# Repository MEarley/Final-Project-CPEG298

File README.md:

# Internet of Things Device for a Microbial Fuel Cell: IoT MFC
The purpose of this device is to measure the voltage and the surrounding environment of the said cell for research purposes.

## Schematic of SMART MFC (KiCAD)

## SMART MFC CAM
### Front 									

### Back

## SMART MFC BOM

## Arduino code
The entire Arduino sketch is divided into 3 main functions: setup(), loop(), and espData(). 

##### Note: There is also a very minor calculateVoltage() function. However, this is rather self-explanatory. 

The setup() function begins by setting up the serial monitor and the ESP8266 to a baud rate of 9600. Using the ESP8266, it connects to the internet to access Adafruit IO using both usernames and passwords given by the user. After the ESP8266 has successfully connected to Adafruit, analog pins for the light sensor, soil moisture sensor, and voltage reader are set. In addition, the DHT20 is set up using the freely accessible library by Rob Tillaart.

Within the loop() function, the entire block of code repeats every ~5 seconds. This delay is due to the fact that Adafruit only allows a maximum of 30 uploads/minute for free. Using the analogRead() function from the Arduino library, the Arduino Uno collects data in relation to the light, soil moisture, and voltage levels. In addition, the DHT20 library is used to get the humidity and temperature values from the DHT20 sensor. After each reading, the data is transmitted through the ESP8266 to Adafruit where it can be graphically displayed. This loop() function also sets threshold values for the soil moisture level and the temperature values.

Within the espData() function, the given command and data are sent to the ESP8266 using Serial UART. After the data has been sent, the function waits for a response from the ESP8266. This leads to the function printing out the response within the Serial Monitor where it can be viewed for debugging purposes.

## Libraries and Additional Sources
 • Arduino.h
 
 • Wire.h

 • SoftwareSerial.h | Allows usage of two GPIO pins for a second UART

 • DHT20.h | Allows for easier usage of the DHT20
   ESP8266 Example program provided by Theo Fleck and Rick Martin
   DHT20 Demo code provided by library author Rob Tillaart

## Adafruit Dashboard

### Line Graphs

 • Light Level | Displays the level of light over a given time interval time

 • Soil Moisture Level | Displays the level of moisture in the soil over a given time interval time

 • Voltage | Displays the voltage in millivolts of the MFC in a given time interval time   
### Circle Graphs

 • Soil Moisture Level | Displays the current level of moisture within the soil with thresholds between 250 - 700

 • Temperature | Displays the current temperature with a threshold between 20 - 55℃
### Indicators

 • Soil Moisture Level | Indicates when the current soil moisture level is over 250

•  Temperature Level | Indicates when the current temperature is below 25℃

•  Humidity Bar Graph | Displays current relative humidity

•  Feed | Displays data messages between Adafruit and the ESP8266

## Future Changes
In terms of redesign, the voltmeter on the reader still requires tweaking and is the only leading cause of concern. Its purpose in this project is to measure the produced voltage from a Microbial Fuel Cell, which in itself is like a battery having both a positive and negative node. The rise of concern comes from trying to read the amount of voltage produced by the said battery. The Microbial Fuel Cells, or MFC, that are being used in this report can range from 1 mV to 100 mV or more. 

At first, I attempted to read the voltage directly using analogRead(). However, the voltage could not be read due to the voltage being too small. After further research, I came to the conclusion of two possible solutions. 

Solution #1 is an op-amp with a high gain. However, with a capped supply voltage of 5V and a high range of 1-100+ mV, deciding an appropriate gain may be tricky. This would also require additional wiring and spacing for the PCB layout. 

While Solution #1 has a more hardware approach, Solution #2 approaches the problem through the software and proved to be more successful to an extent. Solution #2 is what is seen in the current design: the calculateVoltage() function. This function changes the reference voltage from the default 5V to 1,1V. This allows me to measure the number of millivolts directly from the MFC. While experimenting with a standalone program and an empty Arduino board, this solution works fine. However, in practice, there are further complications. After connecting the MFC’s positive voltage to its corresponding analog pin and its negative terminal to GND, the introduction of this power source causes interference within the other sensors: most notably, the soil moisture sensor. Both the soil moisture sensor and voltmeter begin producing the wrong results at an extreme degree. My assumption is that the amount of noise generated in GND by the other components on the board is too much for the millivolts reader. To improve this design, I would first need to learn how to reduce/diminish the cause of this disruption.

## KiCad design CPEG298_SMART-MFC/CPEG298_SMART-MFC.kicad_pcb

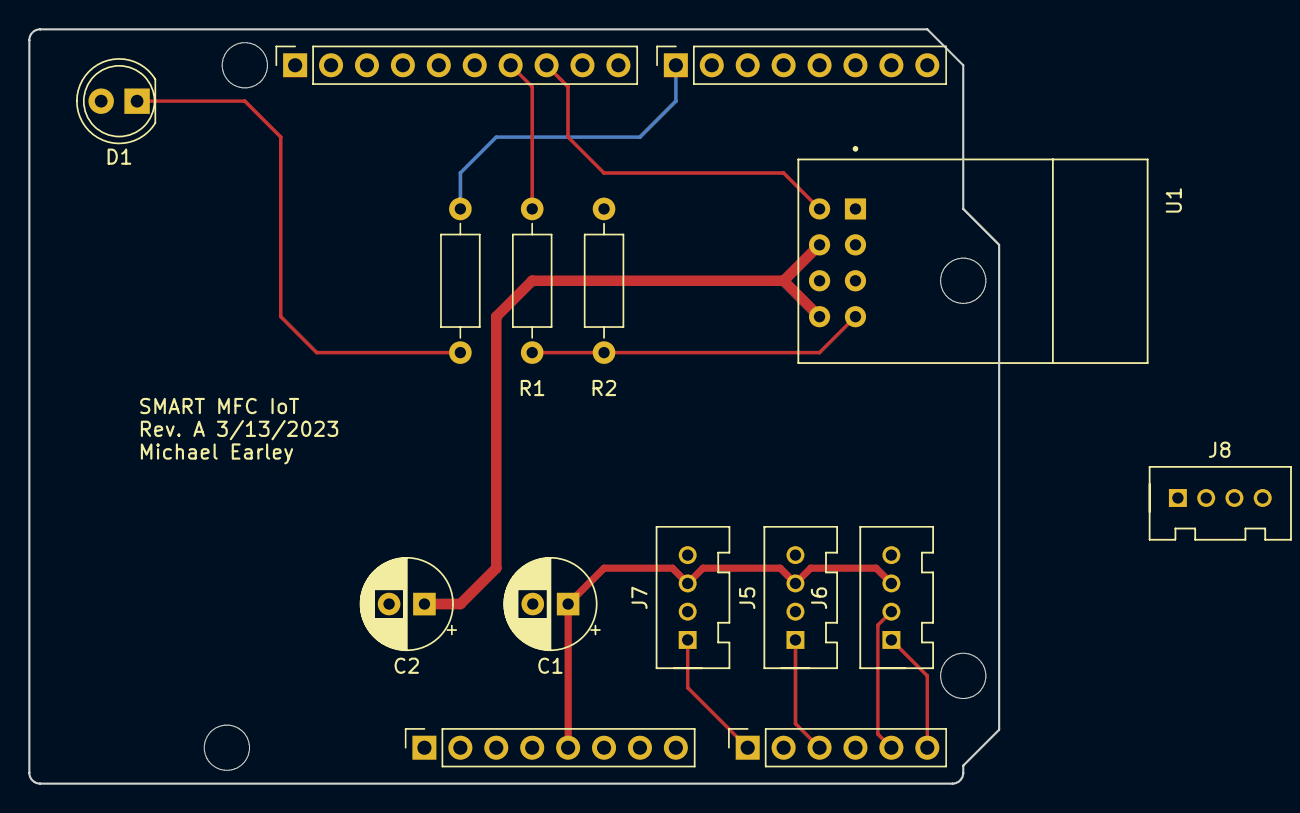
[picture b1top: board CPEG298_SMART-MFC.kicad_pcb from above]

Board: 2 copper layers, 68.6 x 53.3 mm, 19 parts (0 on the bottom side), 12 nets.

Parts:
C1, C2: C_Polarized_US; CP_Radial_D6.3mm_P2.50mm
D1: Soil Moisture Threshold; LED_D5.0mm
J1: Power; PinSocket_1x08_P2.54mm_Vertical
J2: Digital/PWM; PinSocket_1x10_P2.54mm_Vertical
J3: Analog; PinSocket_1x06_P2.54mm_Vertical
J4: Digital/PWM; PinSocket_1x08_P2.54mm_Vertical
J5: Soil_Moisture_Sensor; HW4-2.0
J6: Temperature_Sensor; HW4-2.0
J7: Light_Sensor; HW4-2.0
J8: LCD; HW4-2.0
MH1, MH2, MH3, MH4: MountingHole_3.2mm
R1: 1000; R_Axial_DIN0207_L6.3mm_D2.5mm_P10.16mm_Horizontal
R2: 2000; R_Axial_DIN0207_L6.3mm_D2.5mm_P10.16mm_Horizontal
R3: R; R_Axial_DIN0207_L6.3mm_D2.5mm_P10.16mm_Horizontal
U1: ESP8266-01/ESP-01; XCVR_ESP8266-01_ESP-01

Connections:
+3.3V: C2.1, U1.6 (EN), U1.8 (VCC)
+5V: C1.1, J1.5, J5.3, J6.3, J7.3
/7: J4.1, R3.1
/*10: J2.8, U1.5 (TXD)
/*11: J2.7, R1.1
/A0: J3.1, J7.1
/A2: J3.3, J5.1
/A4: J3.5, J6.2
/A5: J3.6, J6.1
GND: C1.2, C2.2, D1.2 (A), J1.6, J1.7, J2.4, J5.4, J6.4, J7.4, R2.2, U1.1 (GND)
unnamed: D1.1 (K), R3.2
unnamed: R1.2, R2.1, U1.4 (RXD)

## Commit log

2023-03-01 KiCad Schematic from Template
    -Starting of project
    * Uses Arduino Uno Shield Template
2023-03-01 PCB and Schematic Updates
    -Added ESP8266-01_ESP-01 Library from snapeda
    -Added ESP8266-01_ESP-01 to schematic
    -Added capacitor bypass
    -Added ground plate to PCB (Back Copper)
2023-03-02 Code
2023-03-02 Updated
    -Trying to fix temp sensor
2023-03-03 Lab4_Complete
2023-03-08 BMP280
2023-03-09 Lab5
    -Added Grove Connectors
    -Rewiring
    -3D STEP Files
    -New Libraries
    *SEEED, Digikey
2023-03-15 KiCad Components and Software
2023-03-15 KiCad & Code
    -Labeling on PCB
    -Preparing code for millivolt reader
2023-03-20 Submission for Review
2023-08-29 Create README.md
    -Transferred written report
    -Readjusted text types
2023-09-03 Update README.md
    -Added Images
2023-09-04 Added Photos
    -Added photos for documentary
    -Added additional docs/image folder
2023-09-04 Update README.md
    -Fixed photo links (should now be permanent)
